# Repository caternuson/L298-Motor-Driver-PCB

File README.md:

# L298 Motor Driver PCB
EAGLE files for L298 Dual H-Bridge Motor Driver Board. Also available at [OSH Park](https://oshpark.com/shared_projects/nI35iXkY).

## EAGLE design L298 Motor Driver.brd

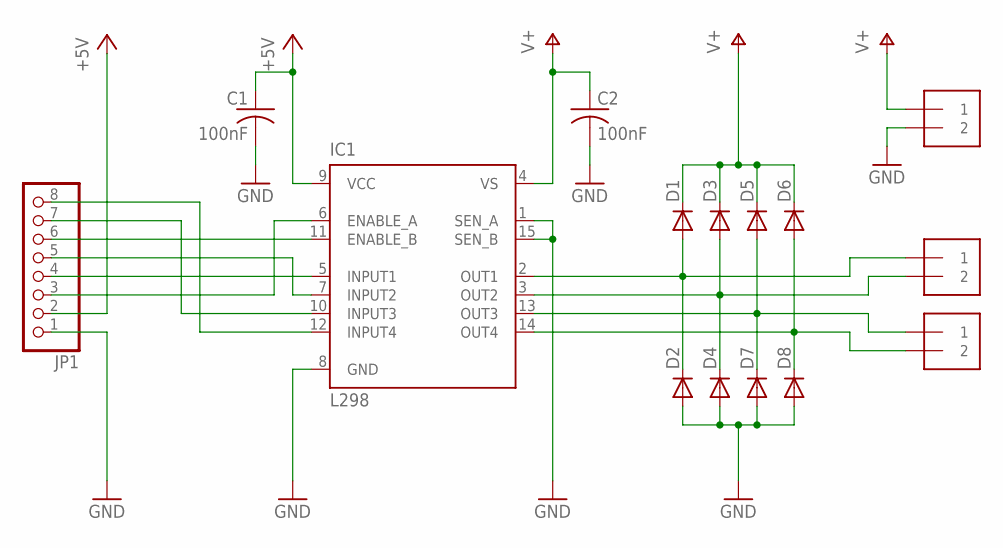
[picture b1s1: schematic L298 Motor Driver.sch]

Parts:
C1, C2: 100nF; C050-024X044
D1, D2, D3, D4, D5, D6, D7, D8: DIODE-D-5; D-5
IC1: L298; MULTIWATT-15
J1, J2, J3: 1X2-3.5MM
JP1: PINHD-1X8; 1X08

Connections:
+5V: C1.1, IC1.9 (VCC), JP1.2
GND: C1.2, C2.2, D2.A, D4.A, D7.A, D8.A, IC1.1 (SEN_A), IC1.8 (GND), IC1.15 (SEN_B), J1.2, JP1.1
unnamed: D1.A, D2.C, IC1.2 (OUT1), J2.1
unnamed: D3.A, D4.C, IC1.3 (OUT2), J2.2
unnamed: D6.A, D8.C, IC1.14 (OUT4), J3.2
unnamed: D5.A, D7.C, IC1.13 (OUT3), J3.1
unnamed: IC1.5 (INPUT1), JP1.4
unnamed: IC1.7 (INPUT2), JP1.5
unnamed: IC1.6 (ENABLE_A), JP1.3
unnamed: IC1.11 (ENABLE_B), JP1.6
unnamed: IC1.10 (INPUT3), JP1.7
unnamed: IC1.12 (INPUT4), JP1.8
V+: C2.1, D1.C, D3.C, D5.C, D6.C, IC1.4 (VS), J1.1

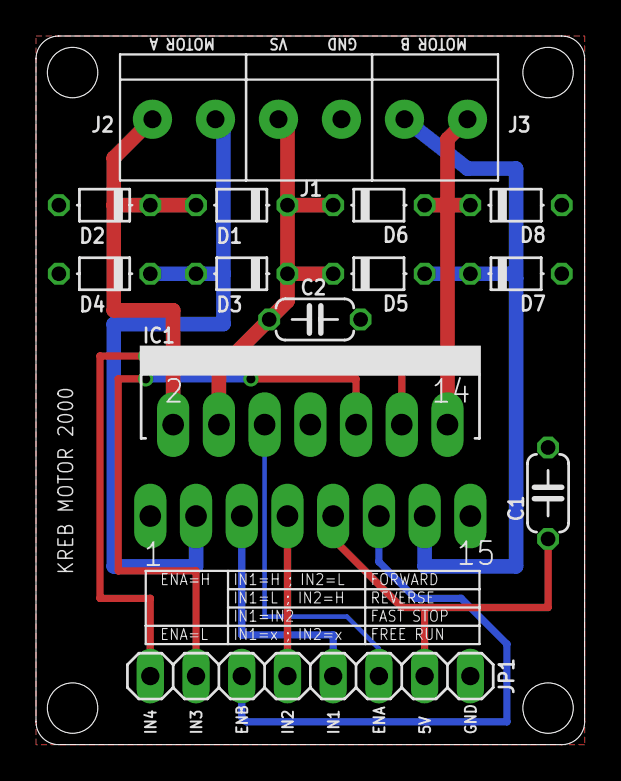
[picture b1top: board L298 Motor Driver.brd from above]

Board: 2 copper layers, 30.5 x 39.4 mm, 15 parts (0 on the bottom side), 13 nets.

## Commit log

2016-07-01 Create LICENSE
2016-07-01 Added info to title block
